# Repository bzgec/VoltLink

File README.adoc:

= VoltLink™
:toc:
:sectnums:
:sectnumlevels: 4

* Current version: *0.1*
* link:./CHANGELOG.adoc[Changelog]

To enable TX and RX LEDs use `cp210x-cfg`.
1. Go to `cp210x-cfg` folder
2. `make`
3. `./cp210x-cfg -L 1`

'''

== Original author's README - ish

link:https://github.com/voltlog/VoltLink[Original repository]

VoltLink™ is a USB to serial adapter board based on the popular CP2102N chip with built-in ESP32 auto-reset circuitry.
When compared to the cheap modules you can get from Aliexpress this adapter is reliable & flexible at the same time.
Reliable because it's based on a well known usb to serial adapter chip sourced from a known supplier and flexible because you have the ESP32 IO & EN pin auto-reset circuit built-in so there is no need to implement this on the target board.

You have the option of connecting through the VoltLink connector which is a JST-SH 1.0mm pitch 6 pin connector that saves space on the target board or via standard 0.1 inch pin header.

If you would like to order one of these adapters ready assembled, check out my link:https://www.tindie.com/products/23076/[Tindie store].

More info about this project in:

* link:https://www.youtube.com/watch?v=bfN77jT1SVE[Voltlog #356 - VoltLink A Fancy USB Serial Adapter (ESP32 Programmer)].
* link:https://www.youtube.com/watch?v=roMjPoaFAZ8[Voltlog #357 - A fatal error occurred: Failed to connect to ESP32]
* link:https://www.youtube.com/watch?v=hDepAs7ljAk[Voltlog #396 - VoltLink™ revB CP2102N USB Serial Bridge & ESP32 Programmer]

== Automated exporting
=== Installation
==== KiBot
link:https://github.com/INTI-CMNB/kibot#installation-using-pip[Installation]:

* `pip install --no-compile kibot`
(on Windows you probably need to install it in `KiCad Command Prompt`)

* On Arch Linux you can install it with: `paru -S kibot-git`
** You may need to install `pcbdraw-git` in case of
`module 'pcbnew' has no attribute 'PLOTTEXTMODE_STROKE'` error
(try to run `pcbnew --version` to be sure that program runs correctly)
** You also may need to install `imagemagick`: `sudo pacman -S imagemagick`
** You also may need to install few `pip` packages: `pip install mistune pybars3 wand`

==== recordmydesktop
* Needed only if running `kibot -vvv`
* Arch Linux: `sudo pacman -S recordmydesktop`

== TODO

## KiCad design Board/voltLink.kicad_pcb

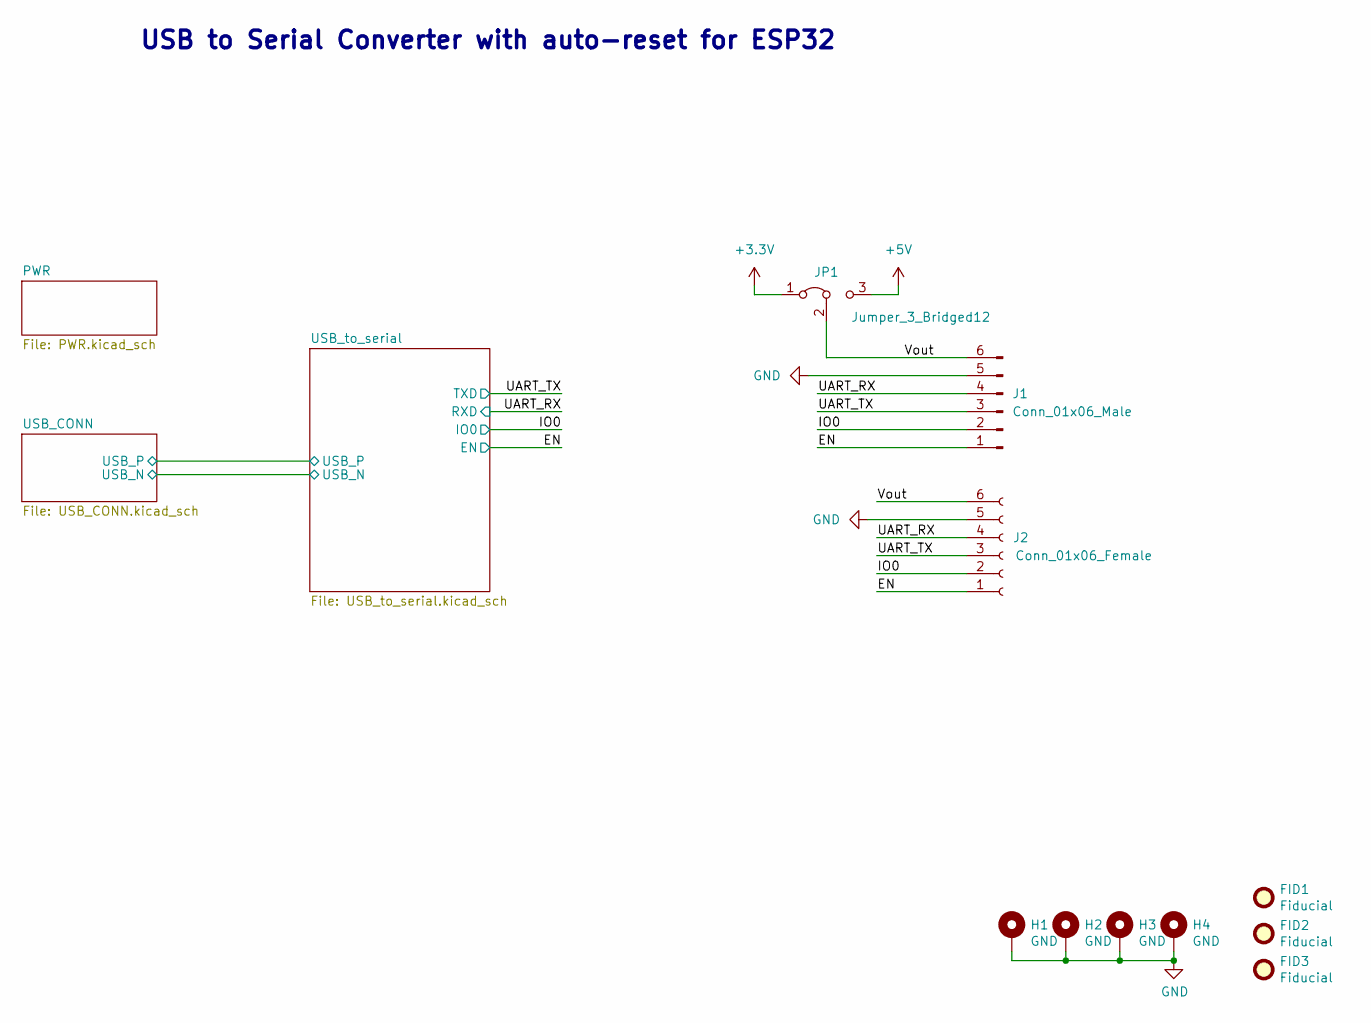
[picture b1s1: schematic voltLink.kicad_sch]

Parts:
FID1, FID2, FID3: Fiducial; Fiducial_0.5mm_Mask1mm
H1, H2, H3, H4: GND; MountingHole_2.5mm_Pad
J1: Conn_01x06_Male; PinHeader_1x06_P2.54mm_Horizontal
J2: Conn_01x06_Female; JST_SH_BM06B-SRSS-TB_1x06-1MP_P1.00mm_Vertical
JP1: Jumper_3_Bridged12; PinHeader_1x03_P2.54mm_Vertical

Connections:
+3V3: JP1.1 (A); also elsewhere on the board
+5V: JP1.3 (B); also elsewhere on the board
/EN: J1.1, J2.1; also elsewhere on the board
/IO0: J1.2, J2.2; also elsewhere on the board
/UART_RX: J1.4, J2.4; also elsewhere on the board
/UART_TX: J1.3, J2.3; also elsewhere on the board
/Vout: J1.6, J2.6, JP1.2 (C)
GND: H1.1, H2.1, H3.1, H4.1, J1.5, J2.5; also elsewhere on the board

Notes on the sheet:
USB to Serial Converter with auto-reset for ESP32

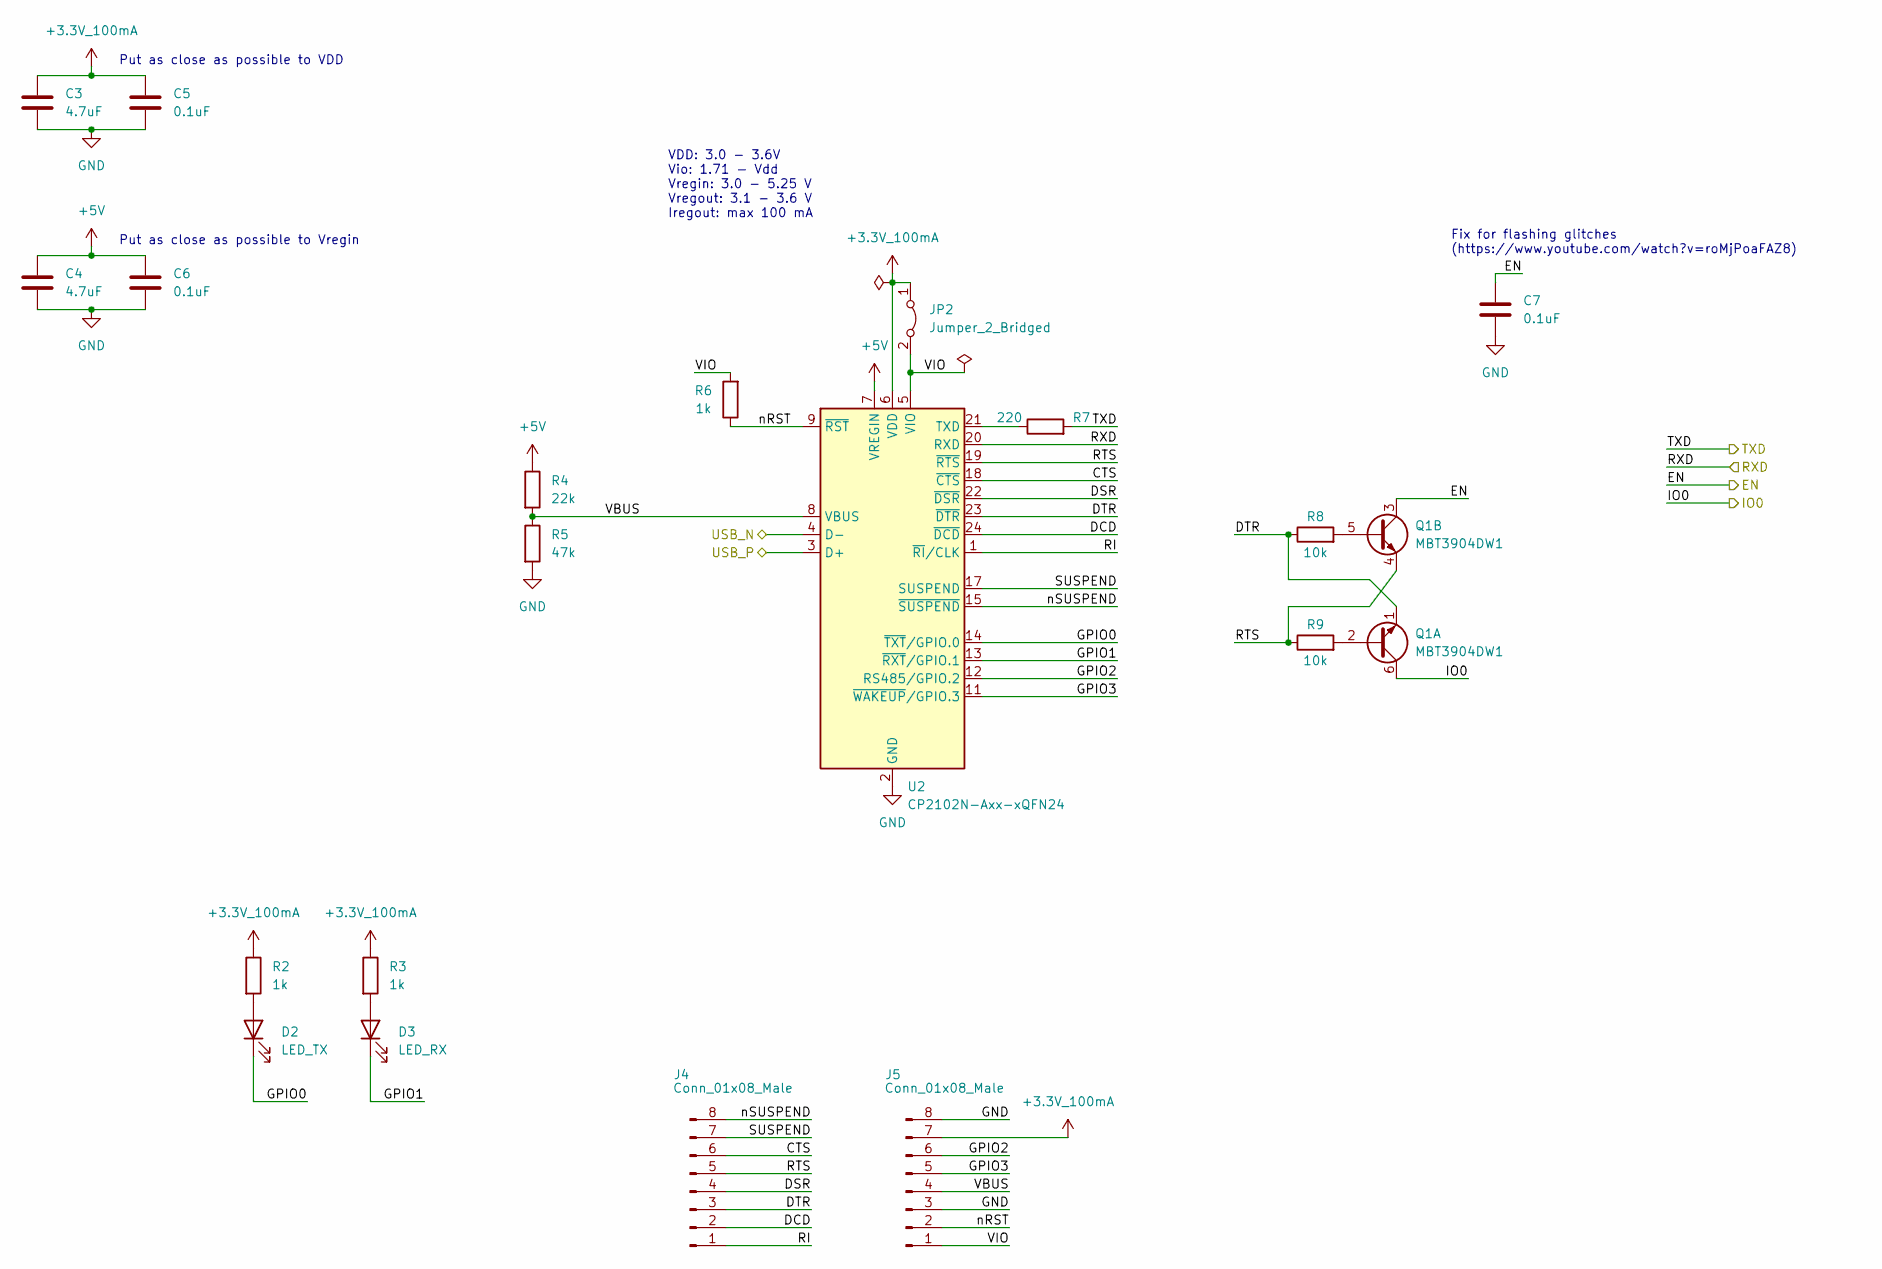
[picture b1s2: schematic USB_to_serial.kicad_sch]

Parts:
C3, C4: 4.7uF; C_0603_1608Metric
C5, C6, C7: 0.1uF; C_0603_1608Metric
D2: LED_TX; D_0603_1608Metric_Pad1.05x0.95mm_HandSolder
D3: LED_RX; D_0603_1608Metric_Pad1.05x0.95mm_HandSolder
J4, J5: Conn_01x08_Male; PinHeader_1x08_P2.54mm_Vertical
JP2: Jumper_2_Bridged; SolderJumper-2_P1.3mm_Bridged_RoundedPad1.0x1.5mm
Q1: MBT3904DW1; SOT-363_SC-70-6
R2, R3, R6: 1k; R_0603_1608Metric
R4: 22k; R_0603_1608Metric
R5: 47k; R_0603_1608Metric
R7: 220; R_0603_1608Metric
R8, R9: 10k; R_0603_1608Metric
U2: CP2102N-Axx-xQFN24; QFN-24-1EP_4x4mm_P0.5mm_EP2.6x2.6mm

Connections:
+3.3V_100mA: C3.1, C5.1, J5.7, JP2.1 (A), R2.1, R3.1, U2.6 (VDD)
+5V: C4.1, C6.1, R4.1, U2.7 (VREGIN); also elsewhere on the board
/EN: C7.1, Q1.3 (C2); also elsewhere on the board
/IO0: Q1.6 (C1); also elsewhere on the board
/UART_RX: U2.20 (RXD); also elsewhere on the board
/UART_TX: R7.2; also elsewhere on the board
/USB_CONN/USB_N: U2.4 (D-); also elsewhere on the board
/USB_CONN/USB_P: U2.3 (D+); also elsewhere on the board
/USB_to_serial/CTS: J4.6, U2.18 (~CTS)
/USB_to_serial/DCD: J4.2, U2.24 (~DCD)
/USB_to_serial/DSR: J4.4, U2.22 (~DSR)
/USB_to_serial/DTR: J4.3, Q1.1 (E1), R8.1, U2.23 (~DTR)
/USB_to_serial/GPIO0: D2.1 (K), U2.14 (~TXT/GPIO.0)
/USB_to_serial/GPIO1: D3.1 (K), U2.13 (~RXT/GPIO.1)
/USB_to_serial/GPIO2: J5.6, U2.12 (RS485/GPIO.2)
/USB_to_serial/GPIO3: J5.5, U2.11 (~WAKEUP/GPIO.3)
/USB_to_serial/RI: J4.1, U2.1 (~RI/CLK)
/USB_to_serial/RTS: J4.5, Q1.4 (E2), R9.1, U2.19 (~RTS)
/USB_to_serial/SUSPEND: J4.7, U2.17 (SUSPEND)
/USB_to_serial/VBUS: J5.4, R4.2, R5.1, U2.8 (VBUS)
/USB_to_serial/VIO: J5.1, JP2.2 (B), R6.2, U2.5 (VIO)
/USB_to_serial/nRST: J5.2, R6.1, U2.9 (~RST)
/USB_to_serial/nSUSPEND: J4.8, U2.15 (~SUSPEND)
GND: C3.2, C4.2, C5.2, C6.2, C7.2, J5.3, J5.8, R5.2, U2.2 (GND), U2.25 (GND); also elsewhere on the board
unnamed: D2.2 (A), R2.2
unnamed: D3.2 (A), R3.2
unnamed: Q1.2 (B1), R9.2
unnamed: Q1.5 (B2), R8.2
unnamed: R7.1, U2.21 (TXD)

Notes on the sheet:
VDD: 3.0 - 3.6V Vio: 1.71 - Vdd Vregin: 3.0 - 5.25 V Vregout: 3.1 - 3.6 V Iregout: max 100 mA
Put as close as possible to VDD
Fix for flashing glitches (https://www.youtube.com/watch?v=roMjPoaFAZ8)
Put as close as possible to Vregin

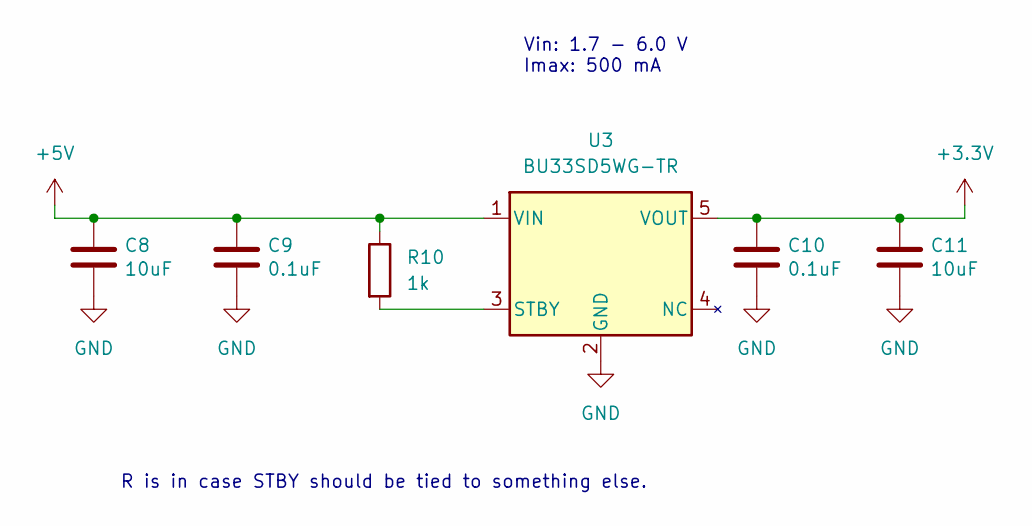
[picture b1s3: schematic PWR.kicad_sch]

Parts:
C8, C11: 10uF; C_0603_1608Metric
C9, C10: 0.1uF; C_0603_1608Metric
R10: 1k; R_0603_1608Metric
U3: BU33SD5WG-TR; SOT-23-5_HandSoldering

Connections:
+3V3: C10.1, C11.1, U3.5 (VOUT); also elsewhere on the board
+5V: C8.1, C9.1, R10.1, U3.1 (VIN); also elsewhere on the board
GND: C8.2, C9.2, C10.2, C11.2, U3.2 (GND); also elsewhere on the board
unnamed: R10.2, U3.3 (STBY)

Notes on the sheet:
Vin: 1.7 - 6.0 V Imax: 500 mA
R is in case STBY should be tied to something else.

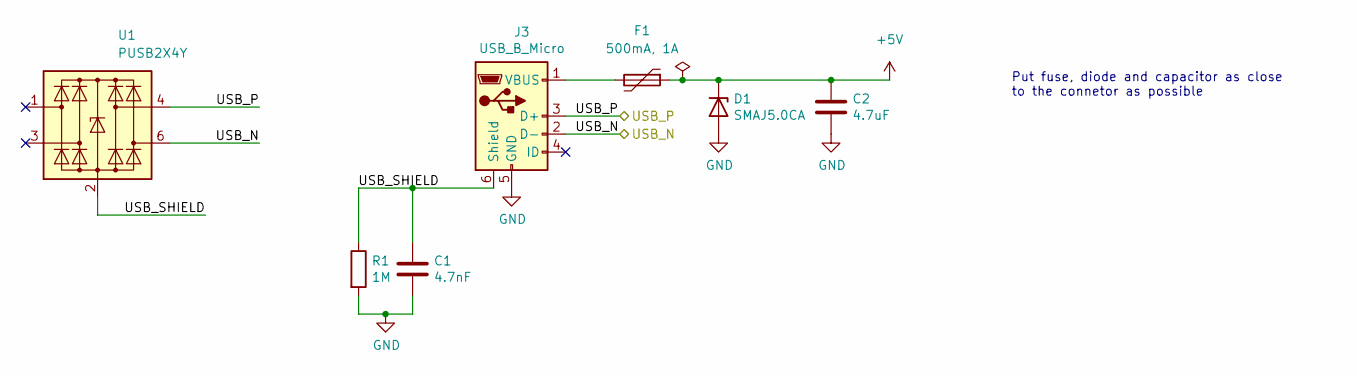
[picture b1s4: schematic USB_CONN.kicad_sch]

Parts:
C1: 4.7nF; C_0603_1608Metric
C2: 4.7uF; C_0603_1608Metric
D1: SMAJ5.0CA; D_SMA
F1: 500mA, 1A; Fuse_1206_3216Metric_Pad1.42x1.75mm_HandSolder
J3: USB_B_Micro; USB_Micro-B_Molex-105017-0001
R1: 1M; R_0603_1608Metric
U1: PUSB2X4Y; SOT-363_SC-70-6

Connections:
+5V: C2.1, D1.1 (K), F1.1; also elsewhere on the board
/USB_CONN/USB_N: J3.2 (D-), U1.6 (I/O4); also elsewhere on the board
/USB_CONN/USB_P: J3.3 (D+), U1.4 (I/O3); also elsewhere on the board
/USB_CONN/USB_SHIELD: C1.1, J3.6 (Shield), R1.1, U1.2 (GND)
GND: C1.2, C2.2, D1.2 (A), J3.5 (GND), R1.2; also elsewhere on the board
unnamed: F1.2, J3.1 (VBUS)

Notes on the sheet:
Put fuse, diode and capacitor as close to the connetor as possible

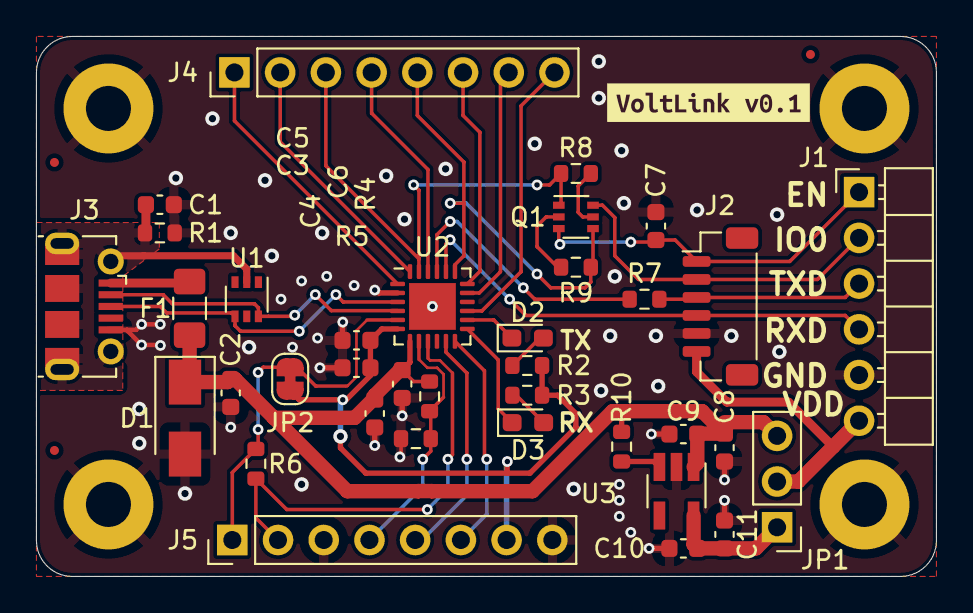
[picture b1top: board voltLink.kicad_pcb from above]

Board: 2 copper layers, 50.0 x 30.0 mm, 44 parts (0 on the bottom side), 34 nets.

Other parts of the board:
kibuzzard-61E57FAE: G***; kibuzzard-61E57FAE

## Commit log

2022-01-17 Change project structure, board redesign
2022-01-17 Rename link to voltLink, fix KiBot export errors
2022-01-17 Add board name and version to PCB (kibuzzard)
2022-01-17 Move some silkscreen
2022-01-18 Change fiducial positions
2022-01-18 Uncomment pcbdraw and pdf_pcb_print in .kibot.yaml
2022-01-18 Add dpi option for pcbdraw in .kibot.yaml
2024-09-25 Add cp210x-cfg submodule to enable RX/TX LEDs

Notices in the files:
Board/voltLink.kicad_sch:
GPL-3.0 License
